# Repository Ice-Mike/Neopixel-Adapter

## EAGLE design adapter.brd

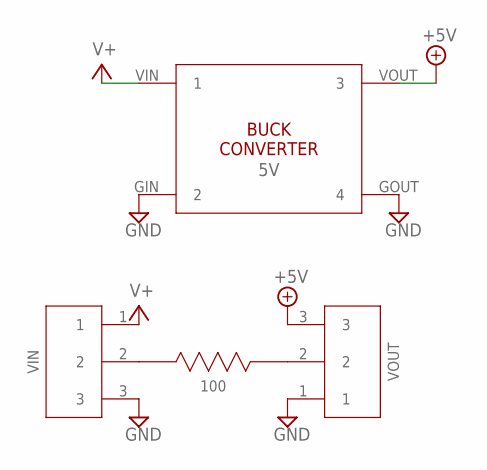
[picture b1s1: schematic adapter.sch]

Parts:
U$1: 5V; BUCK_CONVERTER
U$2: 100; RESISTOR_THROUGHHOLE
VIN: J3PIN
VOUT: J3PIN

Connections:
+5V: U$1.VOUT (3), VOUT.3
GND: U$1.GIN (2), U$1.GOUT (4), VIN.3, VOUT.1
unnamed: U$2.1, VIN.2
unnamed: U$2.2, VOUT.2
V+: U$1.VIN (1), VIN.1

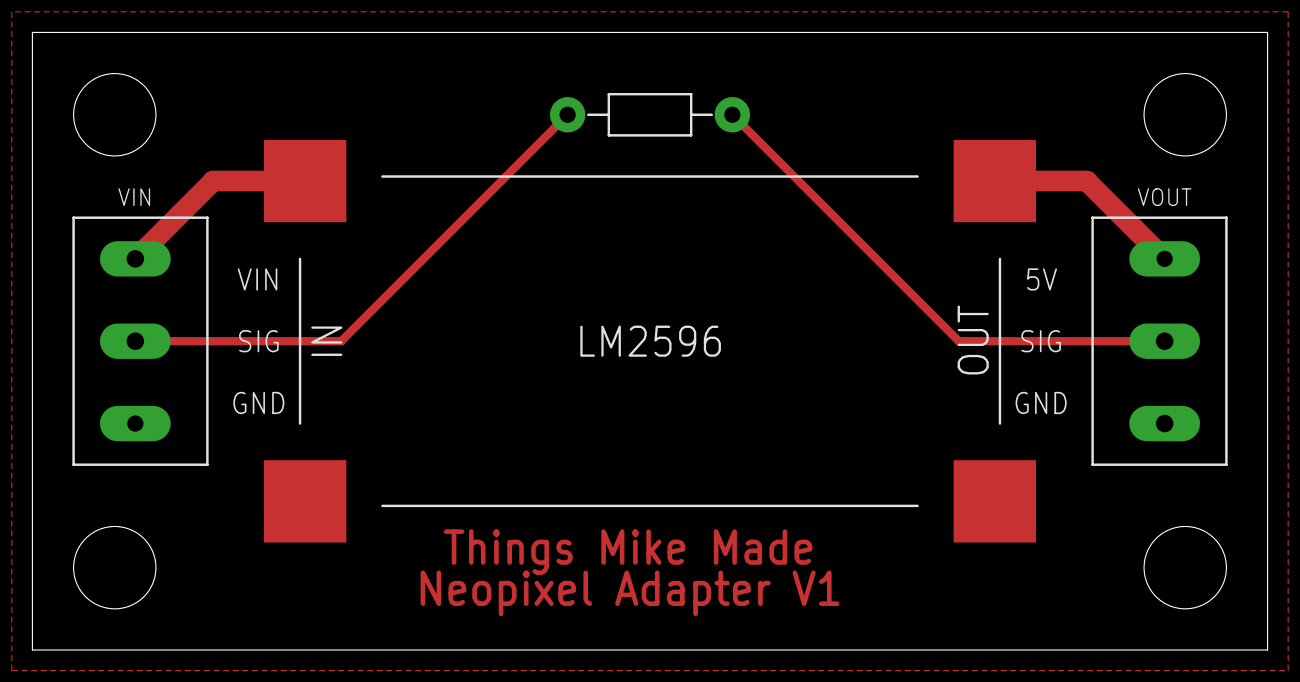
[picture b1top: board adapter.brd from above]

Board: 2 copper layers, 76.2 x 38.1 mm, 4 parts (0 on the bottom side), 5 nets.
